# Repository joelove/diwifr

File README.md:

# diwifr

Diwifr is a 38-key one-piece split keyboard, with full wireless functionality, based on the [Ahokore](https://github.com/dezlidezlidezli/ahokore). Stagger is copied from the Ferris and modified. The name is "wireless" translated into Welsh.

All work in this repository is released into the public domain. See the license file for more details!

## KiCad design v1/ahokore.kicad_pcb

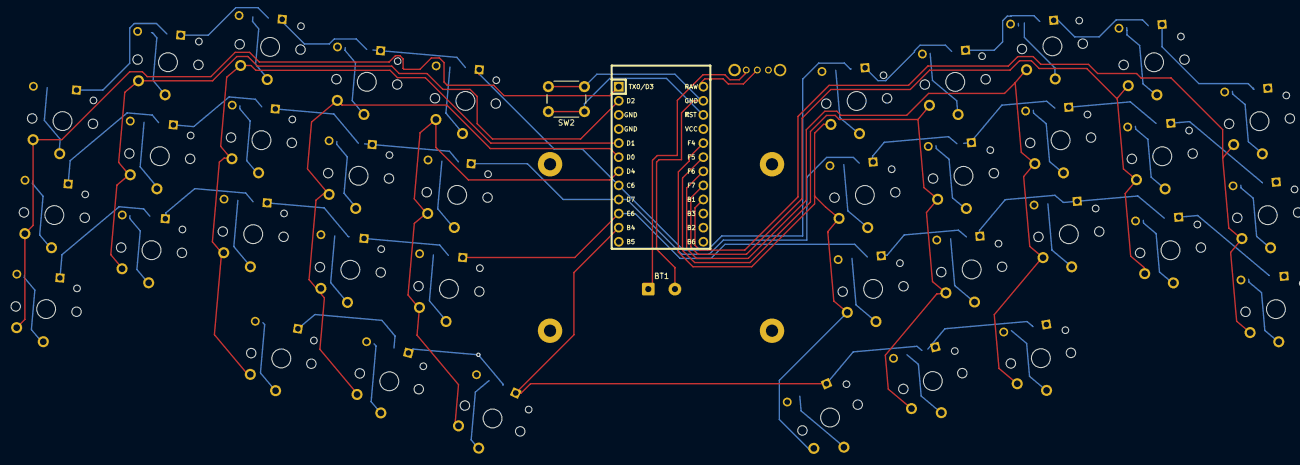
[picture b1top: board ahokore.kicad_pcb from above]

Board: 2 copper layers, 76 parts (0 on the bottom side), 54 nets.

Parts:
BT1: Battery_Cell; battery
D1, D2, D3, D4, D5, D6, D7, D8, D9, D10, D11, D12, D13, D14, D15, D16, D17, D18, D19, D20, D21, D22, D23, D24, D25, D26, D27, D28, D29, D30, D31, D32, D33, D34, D35, D36: D_Small; Diode-Hybrid-Back
SW1: SW_SPDT; OS102011MA1QN1
SW2: SW_Push; SW_PUSH_6mm
SW3, SW4, SW5, SW6, SW7, SW8, SW9, SW10, SW11, SW12, SW13, SW14, SW15, SW16, SW17, SW18, SW19, SW20, SW21, SW22, SW23, SW24, SW25, SW26, SW27, SW28, SW29, SW30, SW31, SW32, SW33, SW34, SW35, SW36, SW37, SW38: SW_Push; customchocfootprint
U1: ProMicro; ArduinoProMicro

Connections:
+BATT: SW1.2, U1.24
COL0: SW3.2, SW13.2, SW23.2, U1.1
COL1: SW4.2, SW14.2, SW24.2, U1.2
COL2: SW5.2, SW15.2, SW25.2, SW33.2, U1.5
COL3: SW6.2, SW16.2, SW26.2, SW34.2, U1.6
COL4: SW7.2, SW17.2, SW27.2, SW35.2, U1.7
COL5: SW8.2, SW18.2, SW28.2, SW36.2, U1.20
COL6: SW9.2, SW19.2, SW29.2, SW37.2, U1.19
COL7: SW10.2, SW20.2, SW30.2, SW38.2, U1.18
COL8: SW11.2, SW21.2, SW31.2, U1.17
COL9: SW12.2, SW22.2, SW32.2, U1.16
GND: BT1.2, SW2.2, U1.23
unnamed: BT1.1, SW1.1
unnamed: D1.2, SW3.1
unnamed: D2.2, SW4.1
unnamed: D3.2, SW5.1
unnamed: D4.2, SW6.1
unnamed: D5.2, SW7.1
unnamed: D6.2, SW8.1
unnamed: D7.2, SW9.1
unnamed: D8.2, SW10.1
unnamed: D9.2, SW11.1
unnamed: D10.2, SW12.1
unnamed: D11.2, SW13.1
unnamed: D12.2, SW14.1
unnamed: D13.2, SW15.1
unnamed: D14.2, SW16.1
unnamed: D15.2, SW17.1
unnamed: D16.2, SW18.1
unnamed: D17.2, SW19.1
unnamed: D18.2, SW20.1
unnamed: D19.2, SW21.1
unnamed: D20.2, SW22.1
unnamed: D21.2, SW23.1
unnamed: D22.2, SW24.1
unnamed: D23.2, SW25.1
unnamed: D24.2, SW26.1
unnamed: D25.2, SW27.1
unnamed: D26.2, SW28.1
unnamed: D27.2, SW29.1
unnamed: D28.2, SW30.1
unnamed: D29.2, SW31.1
unnamed: D30.2, SW32.1
unnamed: D31.2, SW33.1
unnamed: D32.2, SW34.1
unnamed: D33.2, SW35.1
unnamed: D34.2, SW36.1
unnamed: D35.2, SW37.1
unnamed: D36.2, SW38.1
ROW0: D1.1, D2.1, D3.1, D4.1, D5.1, D6.1, D7.1, D8.1, D9.1, D10.1, U1.8
ROW1: D11.1, D12.1, D13.1, D14.1, D15.1, D16.1, D17.1, D18.1, D19.1, D20.1, U1.9
ROW2: D21.1, D22.1, D23.1, D24.1, D25.1, D26.1, D27.1, D28.1, D29.1, D30.1, U1.10
ROW3: D31.1, D32.1, D33.1, D34.1, D35.1, D36.1, U1.11
RST: SW2.1, U1.22

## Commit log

2023-08-15 update pcb kikads
